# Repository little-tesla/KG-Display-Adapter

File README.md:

# KG Display Adapter

A KiCAD-designed replacement adapter PCB for Keisoku Giken electronic loads (tested with **ELS-304**, likely compatible with similar models).

## Overview

This adapter allows the use of a modern **3.3V display module** as a replacement for the original LCD.

- **Compatible display:** [NHD-C12864WC-FSW-FBW-3V3](https://www.newhavendisplay.com/nhdc12864wcfswfbw3v3-p-6365.html)
- **Purpose:** Replaces the obsolete LCD

## Important Notes

- The new display is slightly thicker; during assembly, the **thin clear protective sheet** originally in front of the display must be **omitted**.
- The **original backlight LEDs must be removed**.
- The **adapter’s backlight** should be connected using **two wires** to the front panel PCB.

## Images

3D and PCB views of the adapter:

Integration and connection to the front panel PCB and display:

---

This project is shared for educational and hobbyist purposes. Use at your own risk.

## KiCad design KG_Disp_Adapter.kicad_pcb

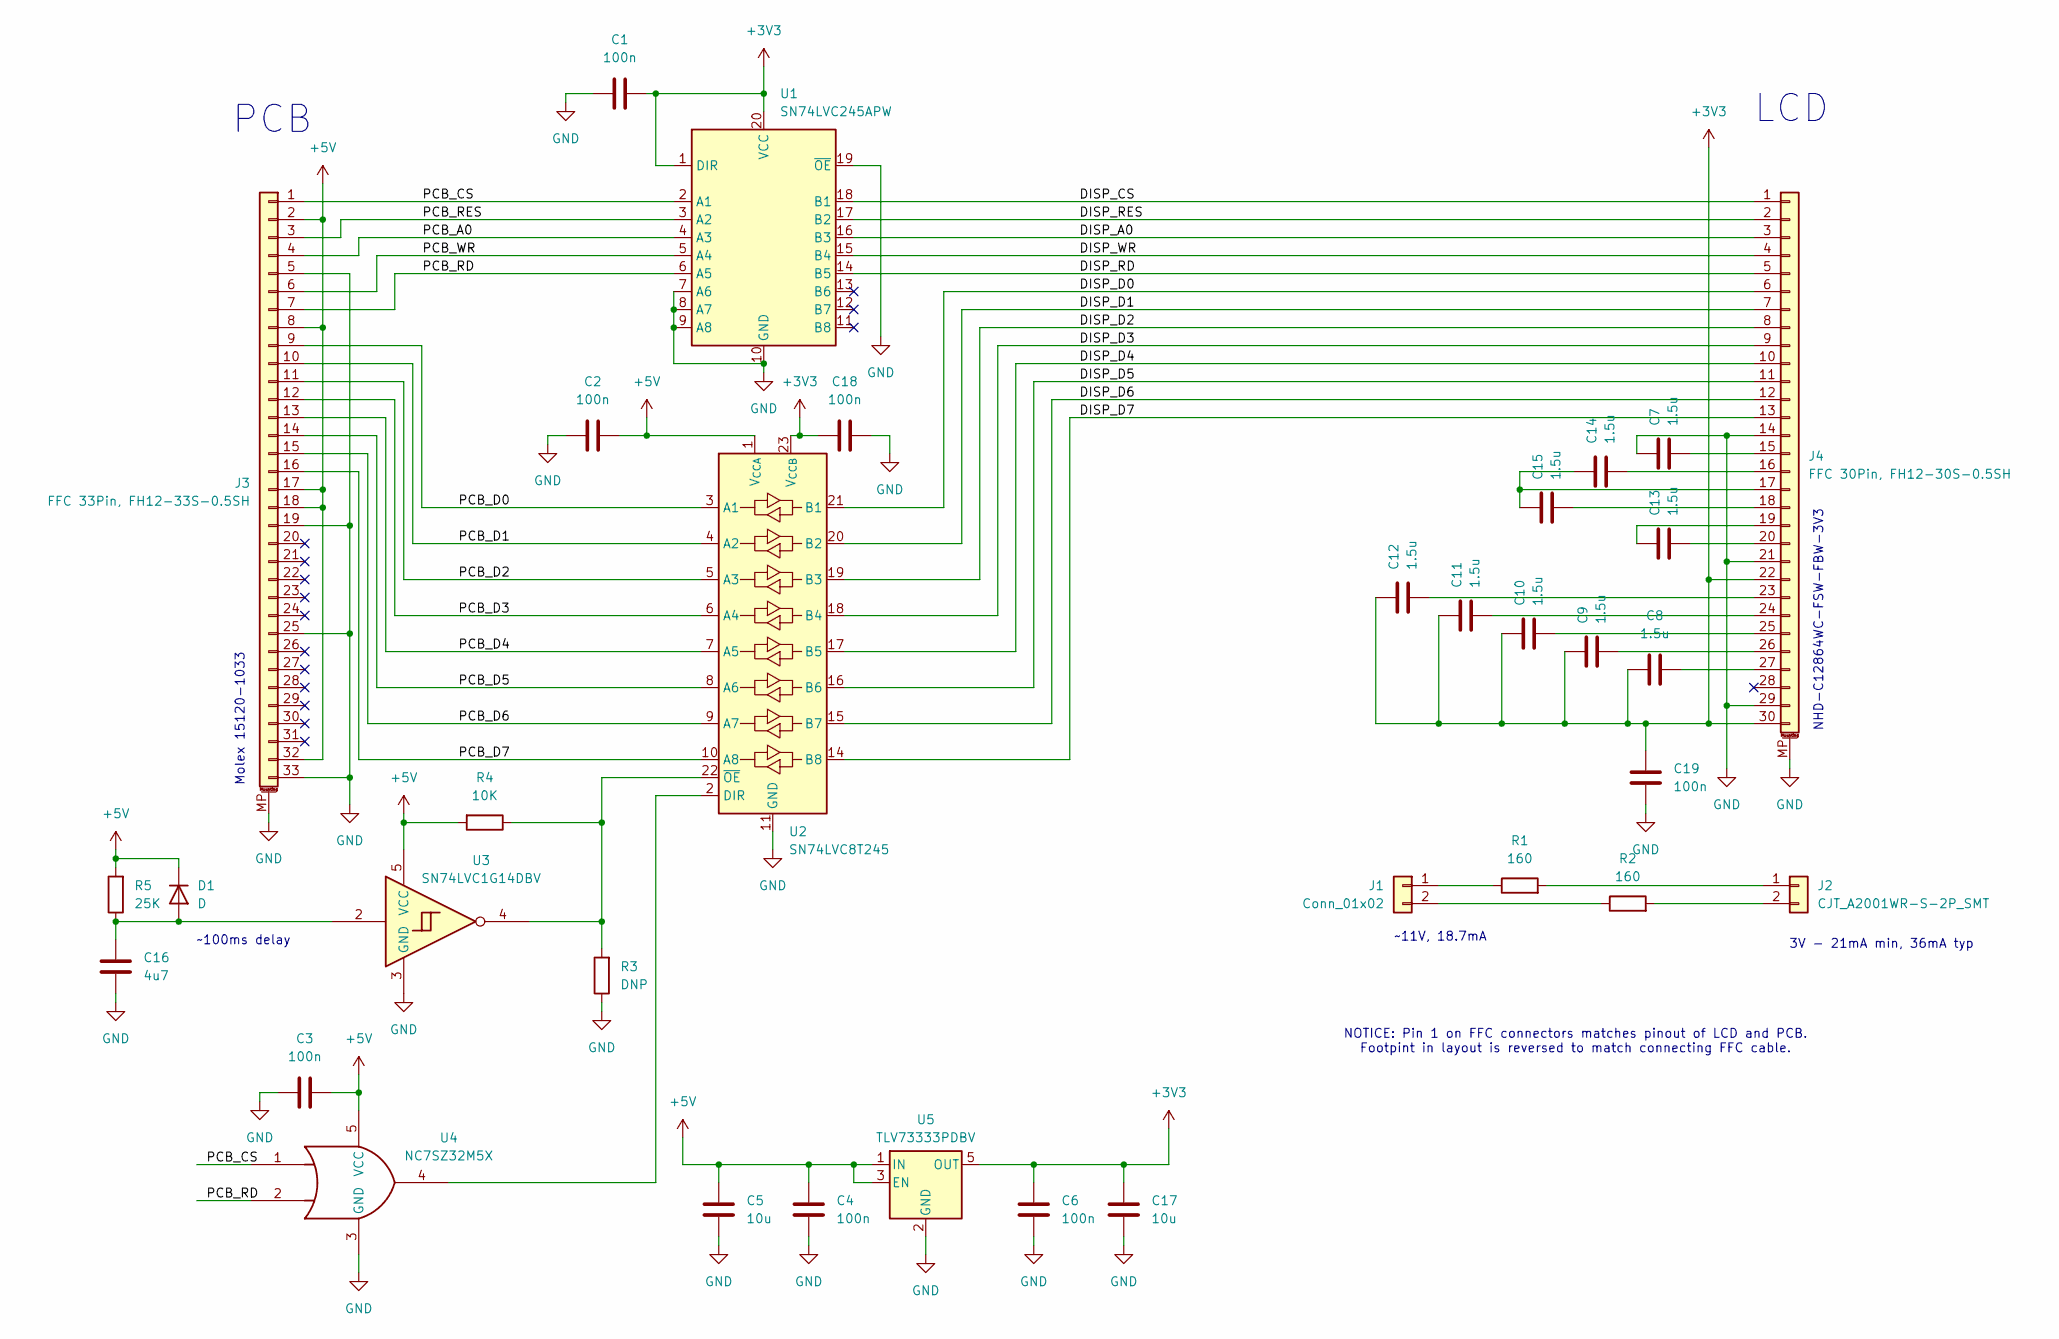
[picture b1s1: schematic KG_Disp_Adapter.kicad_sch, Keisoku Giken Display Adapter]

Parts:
C1, C2, C3, C4, C6, C18, C19: 100n; C_0805_2012Metric
C5, C17: 10u; C_0805_2012Metric
C7, C8, C9, C10, C11, C12, C13, C14, C15: 1.5u; C_0805_2012Metric
C16: 4u7; C_0805_2012Metric
D1: D; D_SOD-323
J1: Conn_01x02; PinHeader_1x02_P1.00mm_Horizontal
J2: CJT_A2001WR-S-2P_SMT; CJT_A2001WR-S-2P_SMT_1x02-1MP_P2.00mm_Horizontal
J3: FFC 33Pin, FH12-33S-0.5SH; Hirose_FH12-33S-0.5SH_1x33-1MP_P0.50mm_Horizontal_reversed
J4: FFC 30Pin, FH12-30S-0.5SH; Hirose_FH12-30S-0.5SH_1x30-1MP_P0.50mm_Horizontal_Reversed
R1, R2: 160; R_0805_2012Metric
R3: DNP; R_0805_2012Metric
R4: 10K; R_0805_2012Metric
R5: 25K; R_0805_2012Metric
U1: SN74LVC245APW; SOIC-20W_7.5x12.8mm_P1.27mm
U2: SN74LVC8T245; TSSOP-24_6.1x7.8mm_P0.65mm
U3: SN74LVC1G14DBV; SOT-23-5
U4: NC7SZ32M5X; SOT-23-5_HandSoldering
U5: TLV73333PDBV; SOT-23-5

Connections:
+3V3: C1.2, C6.2, C8.1, C9.2, C10.2, C11.2, C12.2, C17.2, C18.1, C19.1, J4.22, J4.30, U1.1 (DIR), U1.20 (VCC), U2.23 (V_{CCB}), U2.24 (V_{CCB}), U5.5 (OUT)
+5V: C2.2, C3.2, C4.2, C5.2, D1.1 (K), J3.2, J3.8, J3.17, J3.18, J3.32, R4.2, R5.2, U2.1 (V_{CCA}), U3.5 (VCC), U4.5 (VCC), U5.1 (IN), U5.3 (EN)
/DISP_A0: J4.3, U1.16 (B3)
/DISP_CS: J4.1, U1.18 (B1)
/DISP_D0: J4.6, U2.21 (B1)
/DISP_D1: J4.7, U2.20 (B2)
/DISP_D2: J4.8, U2.19 (B3)
/DISP_D3: J4.9, U2.18 (B4)
/DISP_D4: J4.10, U2.17 (B5)
/DISP_D5: J4.11, U2.16 (B6)
/DISP_D6: J4.12, U2.15 (B7)
/DISP_D7: J4.13, U2.14 (B8)
/DISP_RD: J4.5, U1.14 (B5)
/DISP_RES: J4.2, U1.17 (B2)
/DISP_WR: J4.4, U1.15 (B4)
/PCB_A0: J3.4, U1.4 (A3)
/PCB_CS: J3.1, U1.2 (A1), U4.1
/PCB_D0: J3.9, U2.3 (A1)
/PCB_D1: J3.10, U2.4 (A2)
/PCB_D2: J3.11, U2.5 (A3)
/PCB_D3: J3.12, U2.6 (A4)
/PCB_D4: J3.13, U2.7 (A5)
/PCB_D5: J3.14, U2.8 (A6)
/PCB_D6: J3.15, U2.9 (A7)
/PCB_D7: J3.16, U2.10 (A8)
/PCB_RD: J3.7, U1.6 (A5), U4.2
/PCB_RES: J3.3, U1.3 (A2)
/PCB_WR: J3.6, U1.5 (A4)
GND: C1.1, C2.1, C3.1, C4.1, C5.1, C6.1, C7.2, C16.1, C17.1, C18.2, C19.2, J3.5, J3.19, J3.25, J3.33, J3.MP (MountPin), J4.14, J4.21, J4.29, J4.MP (MountPin), R3.1, U1.7 (A6), U1.8 (A7), U1.9 (A8), U1.10 (GND), U1.19 (~OE), U2.11 (GND), U2.12 (GND), U2.13 (GND), U3.3 (GND), U4.3 (GND), U5.2 (GND)
unnamed: C16.2, D1.2 (A), R5.1, U3.2
unnamed: J1.1, R1.1
unnamed: J1.2, R2.1
unnamed: J2.1, R1.2
unnamed: J2.2, R2.2
unnamed: C7.1, J4.15
unnamed: C14.1, J4.16
unnamed: C14.2, C15.2, J4.17
unnamed: C15.1, J4.18
unnamed: C13.2, J4.19
unnamed: C13.1, J4.20
unnamed: C12.1, J4.23
unnamed: C11.1, J4.24
unnamed: C10.1, J4.25
unnamed: C9.1, J4.26
unnamed: C8.2, J4.27
unnamed: U2.2 (DIR), U4.4
unnamed: R3.2, R4.1, U2.22 (~OE), U3.4

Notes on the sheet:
NHD-C12864WC-FSW-FBW-3V3
3V - 21mA min, 36mA typ
NOTICE: Pin 1 on FFC connectors matches pinout of LCD and PCB. Footpint in layout is reversed to match connecting FFC cable.
Molex 15120-1033
~100ms delay
LCD
~11V, 18.7mA
PCB

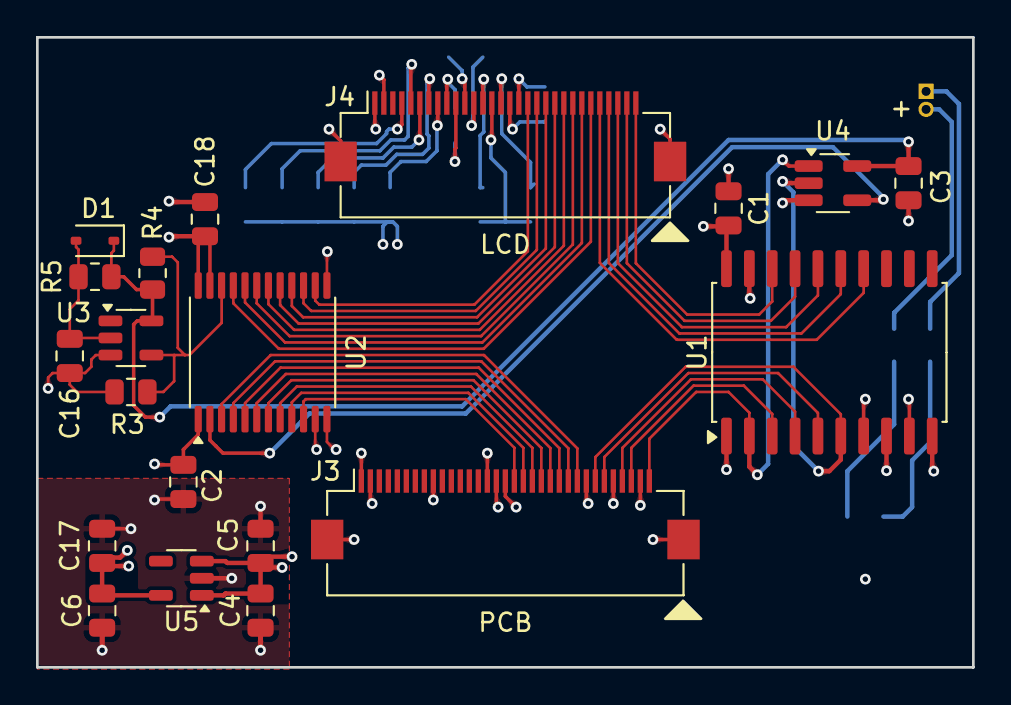
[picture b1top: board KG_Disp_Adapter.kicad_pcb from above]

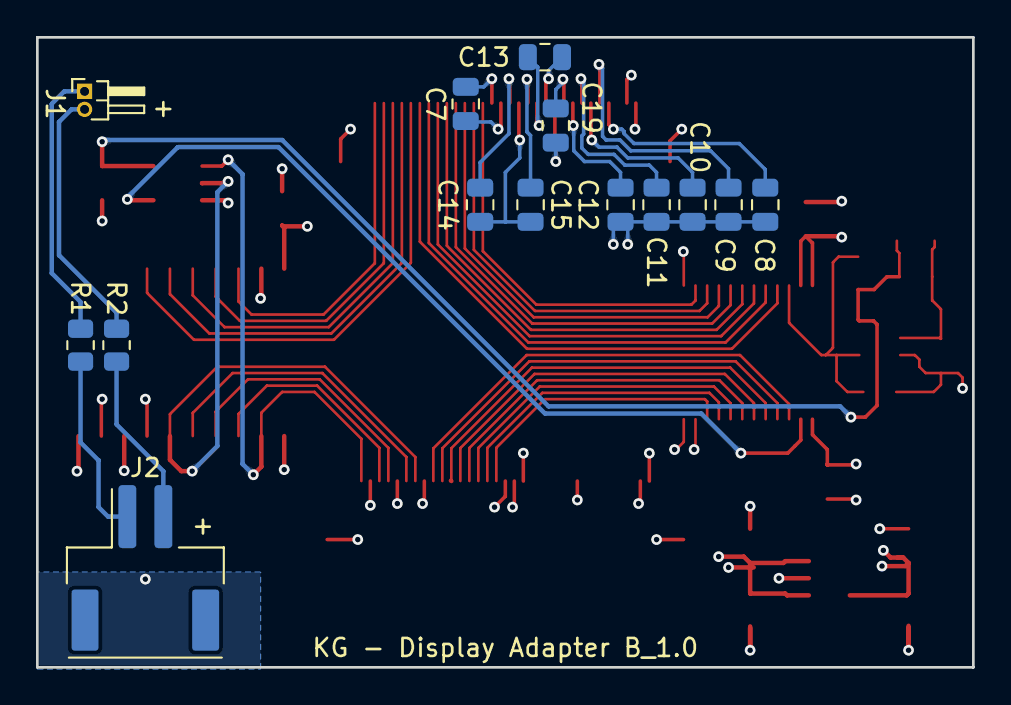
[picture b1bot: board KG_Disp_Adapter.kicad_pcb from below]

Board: 4 copper layers, 52.0 x 35.0 mm, 34 parts (14 on the bottom side), 47 nets.

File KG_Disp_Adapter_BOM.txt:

"Reference","Value","Datasheet","Footprint","Qty","DNP"
"C1,C2,C3,C4,C6,C18,C19","100n","~","Capacitor_SMD:C_0805_2012Metric","7",""
"C5,C17","10u","~","Capacitor_SMD:C_0805_2012Metric","2",""
"C7,C8,C9,C10,C11,C12,C13,C14,C15","1.5u","~","Capacitor_SMD:C_0805_2012Metric","9",""
"C16","4u7","~","Capacitor_SMD:C_0805_2012Metric","1",""
"D1","D","~","Diode_SMD:D_SOD-323","1",""
"J1","Conn_01x02","~","Connector_PinHeader_1.00mm:PinHeader_1x02_P1.00mm_Horizontal","1",""
"J2","CJT_A2001WR-S-2P_SMT","~","Library:CJT_A2001WR-S-2P_SMT_1x02-1MP_P2.00mm_Horizontal","1",""
"J3","FFC 33Pin, FH12-33S-0.5SH","~","Library:Hirose_FH12-33S-0.5SH_1x33-1MP_P0.50mm_Horizontal_reversed","1",""
"J4","FFC 30Pin, FH12-30S-0.5SH","~","Library:Hirose_FH12-30S-0.5SH_1x30-1MP_P0.50mm_Horizontal_Reversed","1",""
"R1,R2","160","~","Resistor_SMD:R_0805_2012Metric","2",""
"R4","10K","~","Resistor_SMD:R_0805_2012Metric","1",""
"R5","25K","~","Resistor_SMD:R_0805_2012Metric","1",""
"U1","SN74LVC245APW","https://www.ti.com/lit/ds/scas218x/scas218x.pdf","Package_SO:SOIC-20W_7.5x12.8mm_P1.27mm","1",""
"U2","SN74LVC8T245","https://www.ti.com/lit/ds/symlink/sn74lvc8t245.pdf","Package_SO:TSSOP-24_6.1x7.8mm_P0.65mm","1",""
"U3","SN74LVC1G14DBV","https://www.ti.com/lit/ds/symlink/sn74lvc1g14.pdf","Package_TO_SOT_SMD:SOT-23-5","1",""
"U4","NC7SZ32M5X","","Package_TO_SOT_SMD:SOT-23-5_HandSoldering","1",""
"U5","TLV73333PDBV","http://www.ti.com/lit/ds/symlink/tlv733p.pdf","Package_TO_SOT_SMD:SOT-23-5","1",""

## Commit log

2025-08-19 Iinitial commit
2025-08-26 Updated license
2025-08-26 improve readme
